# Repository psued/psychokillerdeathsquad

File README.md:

# Psycho Killer Death Squad - FPGA
Branch for Vivado project and docs/utilities for the FPGA.

## Vivado project setup
1. Inside of `fpga/scripts`, run the following command:
```
vivado -mode batch -source create_project.tcl -tclargs custom
```
2. In Vivado, open the .xpr file found inside `fpga/build/custom`

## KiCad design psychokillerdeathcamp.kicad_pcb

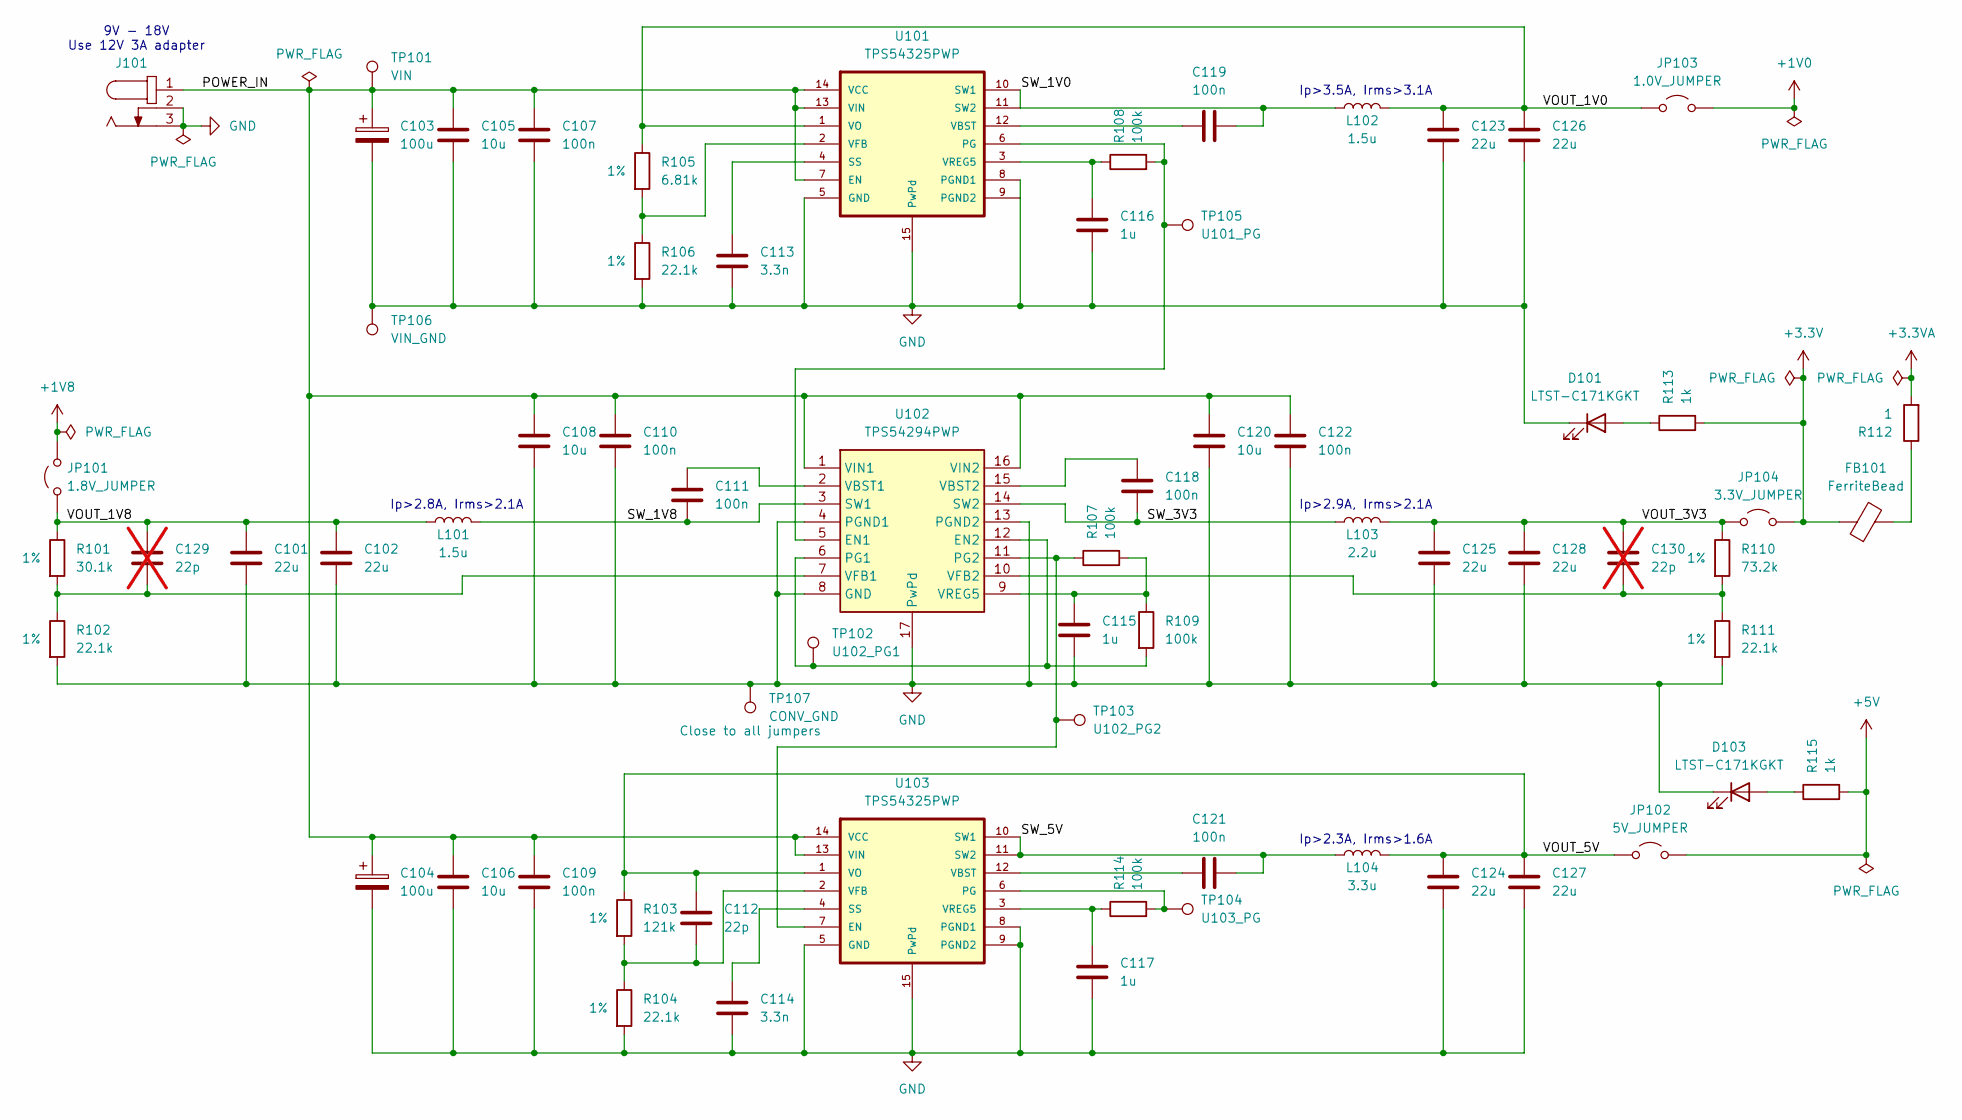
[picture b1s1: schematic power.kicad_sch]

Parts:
C101, C102, C123, C124, C125, C126, C127, C128: 22u; C_1206_3216Metric_Pad1.33x1.80mm_HandSolder
C103, C104: 100u; CP_Elec_6.3x7.7
C105, C106, C108, C120: 10u; C_1206_3216Metric_Pad1.33x1.80mm_HandSolder
C107, C109, C110, C111, C118, C119, C121, C122: 100n; C_0805_2012Metric_Pad1.18x1.45mm_HandSolder
C112: 22p; C_0805_2012Metric_Pad1.18x1.45mm_HandSolder
C113, C114: 3.3n; C_0805_2012Metric_Pad1.18x1.45mm_HandSolder
C115, C116, C117: 1u; C_0805_2012Metric_Pad1.18x1.45mm_HandSolder
C129, C130: 22p; C_0805_2012Metric_Pad1.18x1.45mm_HandSolder; not fitted
D101, D103: LTST-C171KGKT; LED_0805_2012Metric_Pad1.15x1.40mm_HandSolder
FB101: FerriteBead; L_0805_2012Metric_Pad1.05x1.20mm_HandSolder
J101: 694106301002; J_Wurth_WR-DC_694106301002; Working Voltage (V (DC)) 30; Part Number 694106301002
JP101: 1.8V_JUMPER; PinHeader_1x02_P2.54mm_Vertical
JP102: 5V_JUMPER; PinHeader_1x02_P2.54mm_Vertical
JP103: 1.0V_JUMPER; PinHeader_1x02_P2.54mm_Vertical
JP104: 3.3V_JUMPER; PinHeader_1x02_P2.54mm_Vertical
L101, L102: 1.5u; L_Taiyo-Yuden_NR-60xx_HandSoldering
L103: 2.2u; L_Taiyo-Yuden_NR-60xx_HandSoldering
L104: 3.3u; L_Taiyo-Yuden_NR-60xx_HandSoldering
R101: 30.1k; R_0805_2012Metric_Pad1.20x1.40mm_HandSolder; Tolerance 1%
R102, R104, R106, R111: 22.1k; R_0805_2012Metric_Pad1.20x1.40mm_HandSolder; Tolerance 1%
R103: 121k; R_0805_2012Metric_Pad1.20x1.40mm_HandSolder; Tolerance 1%
R105: 6.81k; R_0805_2012Metric_Pad1.20x1.40mm_HandSolder; Tolerance 1%
R107, R108, R109, R114: 100k; R_0805_2012Metric_Pad1.20x1.40mm_HandSolder
R110: 73.2k; R_0805_2012Metric_Pad1.20x1.40mm_HandSolder; Tolerance 1%
R112: 1; R_0805_2012Metric_Pad1.20x1.40mm_HandSolder
R113, R115: 1k; R_0805_2012Metric_Pad1.20x1.40mm_HandSolder
TP101: VIN; TestPoint_Pad_D1.5mm
TP102: U102_PG1; PinHeader_1x01_P2.54mm_Vertical
TP103: U102_PG2; PinHeader_1x01_P2.54mm_Vertical
TP104: U103_PG; PinHeader_1x01_P2.54mm_Vertical
TP105: U101_PG; PinHeader_1x01_P2.54mm_Vertical
TP106: VIN_GND; PinHeader_1x01_P2.54mm_Vertical
TP107: CONV_GND; PinHeader_1x01_P2.54mm_Vertical
U101, U103: TPS54325PWP; Texas_HTSSOP-14-1EP_4.4x5mm_P0.65mm_EP3.4x5mm_Mask2.60x2.59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
U102: TPS54294PWP; HTSSOP-16-1EP_4.4x5mm_P0.65mm_EP3.4x5mm_Mask3.30x3.30mm_The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; Mouser Part Number 595-TPS54294PWP

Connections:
+1V0: JP103.2 (B); also elsewhere on the board
+1V8: JP101.2 (B); also elsewhere on the board
+3.3V: FB101.1, JP104.2 (B), R113.2; also elsewhere on the board
+3.3VA: R112.2; also elsewhere on the board
+5V: JP102.2 (B), R115.2; also elsewhere on the board
/Power/POWER_IN: C103.1, C104.1, C105.1, C106.1, C107.1, C108.1, C109.1, C110.1, C120.1, C122.1, J101.1, TP101.1 (1_1), U101.7 (EN), U101.13 (VIN), U101.14 (VCC), U102.1 (VIN1), U102.16 (VIN2), U103.13 (VIN), U103.14 (VCC)
/Power/SW_1V0: C119.2, L102.1, U101.10 (SW1), U101.11 (SW2)
/Power/SW_1V8: C111.2, L101.2, U102.3 (SW1)
/Power/SW_3V3: C118.2, L103.1, U102.14 (SW2)
/Power/SW_5V: C121.2, L104.1, U103.10 (SW1), U103.11 (SW2)
/Power/VOUT_1V0: C123.1, C126.1, JP103.1 (A), L102.2, R105.1, U101.1 (VO)
/Power/VOUT_1V8: C101.1, C102.1, C129.1, JP101.1 (A), L101.1, R101.1
/Power/VOUT_3V3: C125.1, C128.1, C130.1, JP104.1 (A), L103.2, R110.1
/Power/VOUT_5V: C112.1, C124.1, C127.1, JP102.1 (A), L104.2, R103.1, U103.1 (VO)
GND: C101.2, C102.2, C103.2, C104.2, C105.2, C106.2, C107.2, C108.2, C109.2, C110.2, C113.2, C114.2, C115.2, C116.2, C117.2, C120.2, C122.2, C123.2, C124.2, C125.2, C126.2, C127.2, C128.2, D101.1 (K), D103.1 (K), J101.2, J101.3, R102.2, R104.2, R106.2, R111.2, TP106.1 (1_1), TP107.1 (1_1), U101.5 (GND), U101.8 (PGND1), U101.9 (PGND2), U101.15 (PwPd), U102.4 (PGND1), U102.8 (GND), U102.13 (PGND2), U102.17 (PwPd), U103.5 (GND), U103.8 (PGND1), U103.9 (PGND2), U103.15 (PwPd); also elsewhere on the board
unnamed: D101.2 (A), R113.1
unnamed: D103.2 (A), R115.1
unnamed: FB101.2, R112.1
unnamed: R108.2, TP105.1 (1_1), U101.6 (PG), U102.5 (EN1)
unnamed: C113.1, U101.4 (SS)
unnamed: C119.1, U101.12 (VBST)
unnamed: R105.2, R106.1, U101.2 (VFB)
unnamed: C116.1, R108.1, U101.3 (VREG5)
unnamed: R109.2, TP102.1 (1_1), U102.6 (PG1), U102.12 (EN2)
unnamed: R107.1, TP103.1 (1_1), U102.11 (PG2), U103.7 (EN)
unnamed: C111.1, U102.2 (VBST1)
unnamed: C118.1, U102.15 (VBST2)
unnamed: C129.2, R101.2, R102.1, U102.7 (VFB1)
unnamed: C130.2, R110.2, R111.1, U102.10 (VFB2)
unnamed: C115.1, R107.2, R109.1, U102.9 (VREG5)
unnamed: R114.2, TP104.1 (1_1), U103.6 (PG)
unnamed: C114.1, U103.4 (SS)
unnamed: C121.1, U103.12 (VBST)
unnamed: C112.2, R103.2, R104.1, U103.2 (VFB)
unnamed: C117.1, R114.1, U103.3 (VREG5)

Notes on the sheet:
Ip>2.9A, Irms>2.1A
Ip>2.8A, Irms>2.1A
9V - 18V Use 12V 3A adapter
Ip>3.5A, Irms>3.1A
Ip>2.3A, Irms>1.6A

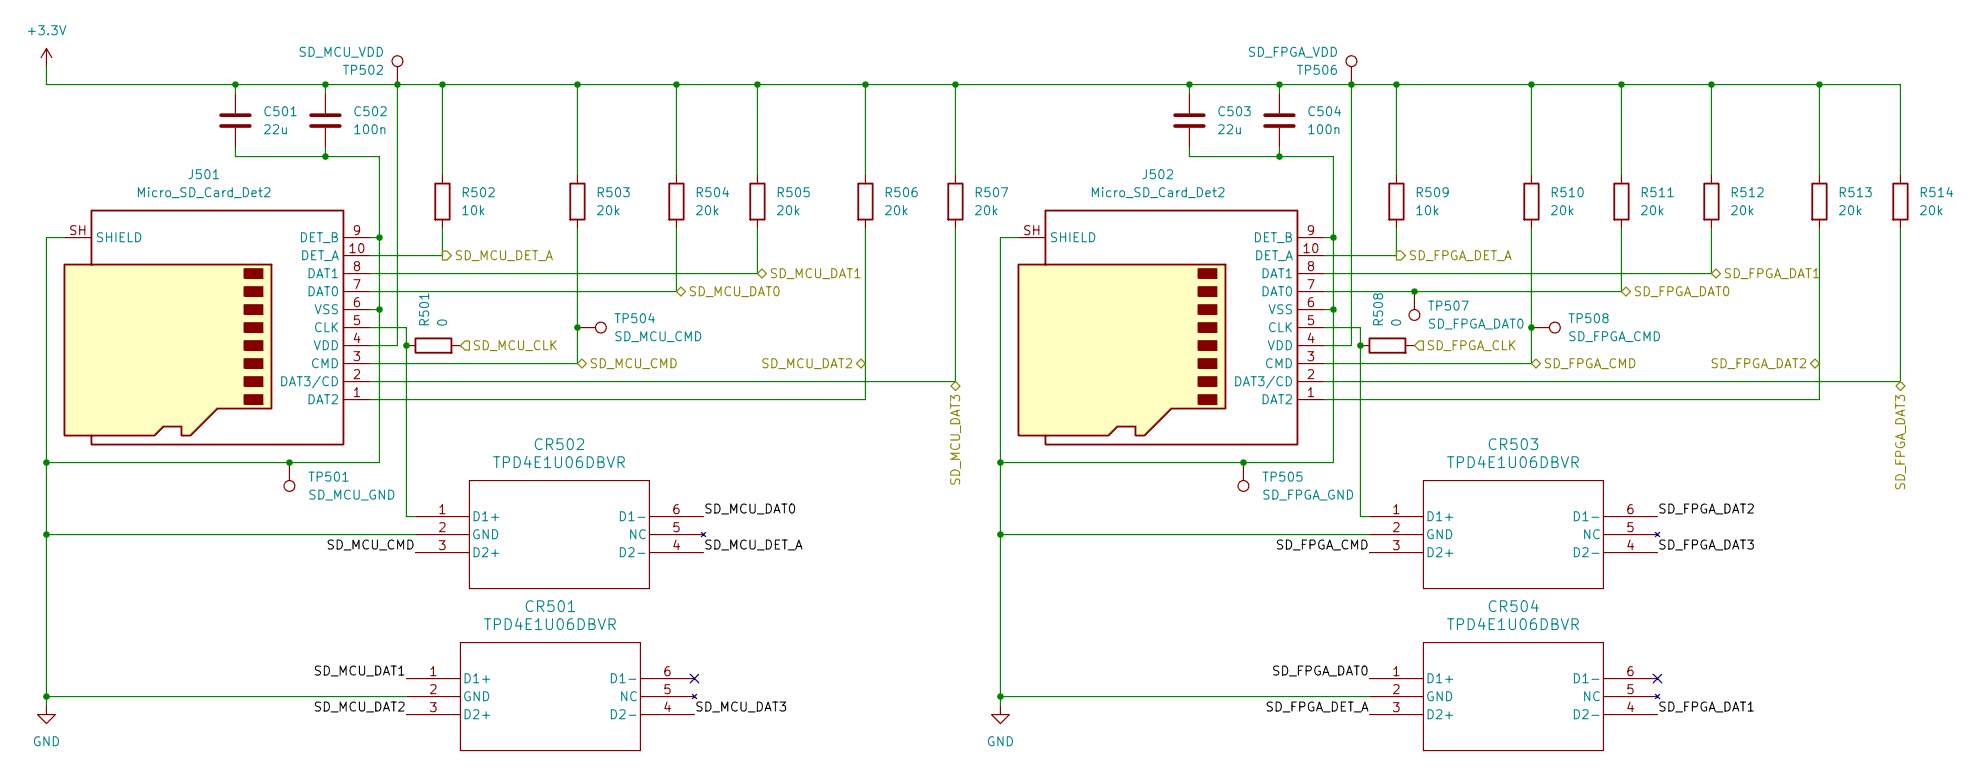
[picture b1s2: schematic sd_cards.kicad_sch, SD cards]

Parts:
C501, C503: 22u; C_1206_3216Metric_Pad1.33x1.80mm_HandSolder
C502, C504: 100n; C_0805_2012Metric_Pad1.18x1.45mm_HandSolder
CR501, CR502, CR503, CR504: TPD4E1U06DBVR
J501, J502: Micro_SD_Card_Det2; 5033981892
R501, R508: 0; R_0805_2012Metric_Pad1.20x1.40mm_HandSolder
R502, R509: 10k; R_0805_2012Metric_Pad1.20x1.40mm_HandSolder
R503, R504, R505, R506, R507, R510, R511, R512, R513, R514: 20k; R_0805_2012Metric_Pad1.20x1.40mm_HandSolder
TP501: SD_MCU_GND; PinHeader_1x01_P2.54mm_Vertical
TP502: SD_MCU_VDD; TestPoint_Pad_D1.5mm
TP504: SD_MCU_CMD; PinHeader_1x01_P2.54mm_Vertical
TP505: SD_FPGA_GND; PinHeader_1x01_P2.54mm_Vertical
TP506: SD_FPGA_VDD; TestPoint_Pad_D1.5mm
TP507: SD_FPGA_DAT0; PinHeader_1x01_P2.54mm_Vertical
TP508: SD_FPGA_CMD; PinHeader_1x01_P2.54mm_Vertical

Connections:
+3.3V: C501.1, C502.1, C503.1, C504.1, J501.4 (VDD), J502.4 (VDD), R502.1, R503.1, R504.1, R505.1, R506.1, R507.1, R509.1, R510.1, R511.1, R512.1, R513.1, R514.1, TP502.1 (1_1), TP506.1 (1_1); also elsewhere on the board
/MCU/SD_MCU_CLK: R501.2; also elsewhere on the board
/SD cards/SD_FPGA_CLK: R508.2; also elsewhere on the board
/SD cards/SD_FPGA_CMD: CR503.3 (D2+), J502.3 (CMD), R510.2, TP508.1 (1_1); also elsewhere on the board
/SD cards/SD_FPGA_DAT0: CR504.1 (D1+), J502.7 (DAT0), R511.2, TP507.1 (1_1); also elsewhere on the board
/SD cards/SD_FPGA_DAT1: CR504.4 (D2-), J502.8 (DAT1), R512.2; also elsewhere on the board
/SD cards/SD_FPGA_DAT2: CR503.6 (D1-), J502.1 (DAT2), R513.2; also elsewhere on the board
/SD cards/SD_FPGA_DAT3: CR503.4 (D2-), J502.2 (DAT3/CD), R514.2; also elsewhere on the board
/SD cards/SD_FPGA_DET_A: CR504.3 (D2+), J502.10 (DET_A), R509.2; also elsewhere on the board
/SD cards/SD_MCU_CMD: CR502.3 (D2+), J501.3 (CMD), R503.2, TP504.1 (1_1); also elsewhere on the board
/SD cards/SD_MCU_DAT0: CR502.6 (D1-), J501.7 (DAT0), R504.2; also elsewhere on the board
/SD cards/SD_MCU_DAT1: CR501.1 (D1+), J501.8 (DAT1), R505.2; also elsewhere on the board
/SD cards/SD_MCU_DAT2: CR501.3 (D2+), J501.1 (DAT2), R506.2; also elsewhere on the board
/SD cards/SD_MCU_DAT3: CR501.4 (D2-), J501.2 (DAT3/CD), R507.2; also elsewhere on the board
/SD cards/SD_MCU_DET_A: CR502.4 (D2-), J501.10 (DET_A), R502.2; also elsewhere on the board
GND: C501.2, C502.2, C503.2, C504.2, CR501.2 (GND), CR502.2 (GND), CR503.2 (GND), CR504.2 (GND), J501.6 (VSS), J501.9 (DET_B), J501.SH (SHIELD), J502.6 (VSS), J502.9 (DET_B), J502.SH (SHIELD), TP501.1 (1_1), TP505.1 (1_1); also elsewhere on the board
unnamed: CR502.1 (D1+), J501.5 (CLK), R501.1
unnamed: CR503.1 (D1+), J502.5 (CLK), R508.1

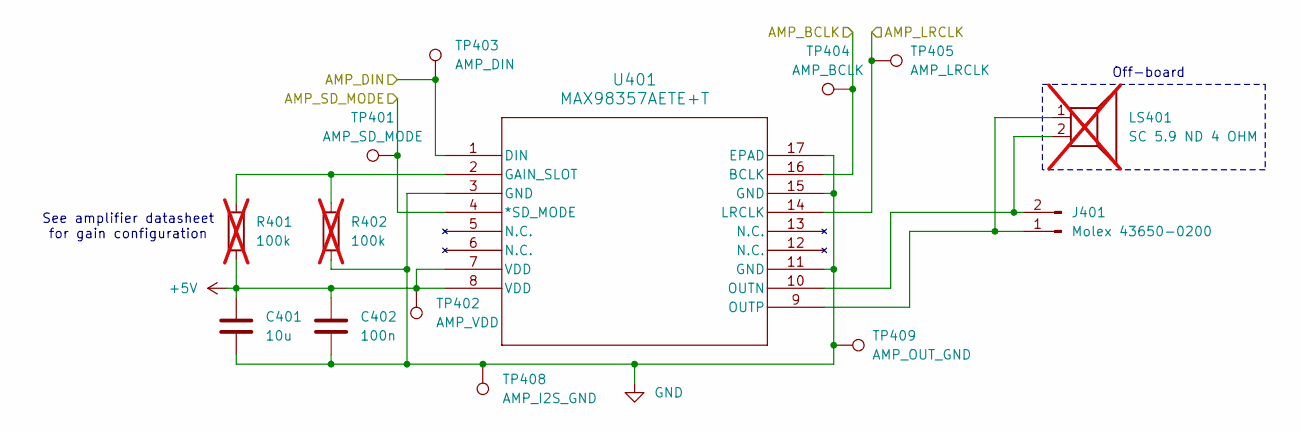
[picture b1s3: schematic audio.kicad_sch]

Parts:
C401: 10u; C_0805_2012Metric_Pad1.18x1.45mm_HandSolder
C402: 100n; C_0805_2012Metric_Pad1.18x1.45mm_HandSolder
J401: Molex 43650-0200; Molex_Micro-Fit_3.0_43650-0200_1x02_P3.00mm_Horizontal
LS401: SC 5.9 ND 4 OHM; not fitted
R401, R402: 100k; R_0805_2012Metric_Pad1.20x1.40mm_HandSolder; not fitted
TP401: AMP_SD_MODE; TestPoint_Pad_D1.5mm
TP402: AMP_VDD; TestPoint_Pad_D1.5mm
TP403: AMP_DIN; PinHeader_1x01_P2.54mm_Vertical
TP404: AMP_BCLK; PinHeader_1x01_P2.54mm_Vertical
TP405: AMP_LRCLK; PinHeader_1x01_P2.54mm_Vertical
TP408: AMP_I2S_GND; PinHeader_1x01_P2.54mm_Vertical
TP409: AMP_OUT_GND; PinHeader_1x01_P2.54mm_Vertical
U401: MAX98357AETE+T; 21-0136I_T1633-4_MXM-M

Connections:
+5V: C401.1, C402.1, R401.2, TP402.1 (1_1), U401.7 (VDD), U401.8 (VDD); also elsewhere on the board
/Audio/AMP_BCLK: TP404.1 (1_1), U401.16 (BCLK); also elsewhere on the board
/Audio/AMP_DIN: TP403.1 (1_1), U401.1 (DIN); also elsewhere on the board
/Audio/AMP_LRCLK: TP405.1 (1_1), U401.14 (LRCLK); also elsewhere on the board
/Audio/AMP_SD_MODE: TP401.1 (1_1), U401.4 (*SD_MODE); also elsewhere on the board
GND: C401.2, C402.2, R402.2, TP408.1 (1_1), TP409.1 (1_1), U401.3 (GND), U401.11 (GND), U401.15 (GND), U401.17 (EPAD); also elsewhere on the board
unnamed: J401.1, LS401.1, U401.9 (OUTP)
unnamed: J401.2, LS401.2, U401.10 (OUTN)
unnamed: R401.1, R402.1, U401.2 (GAIN_SLOT)

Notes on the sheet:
Off-board
See amplifier datasheet for gain configuration

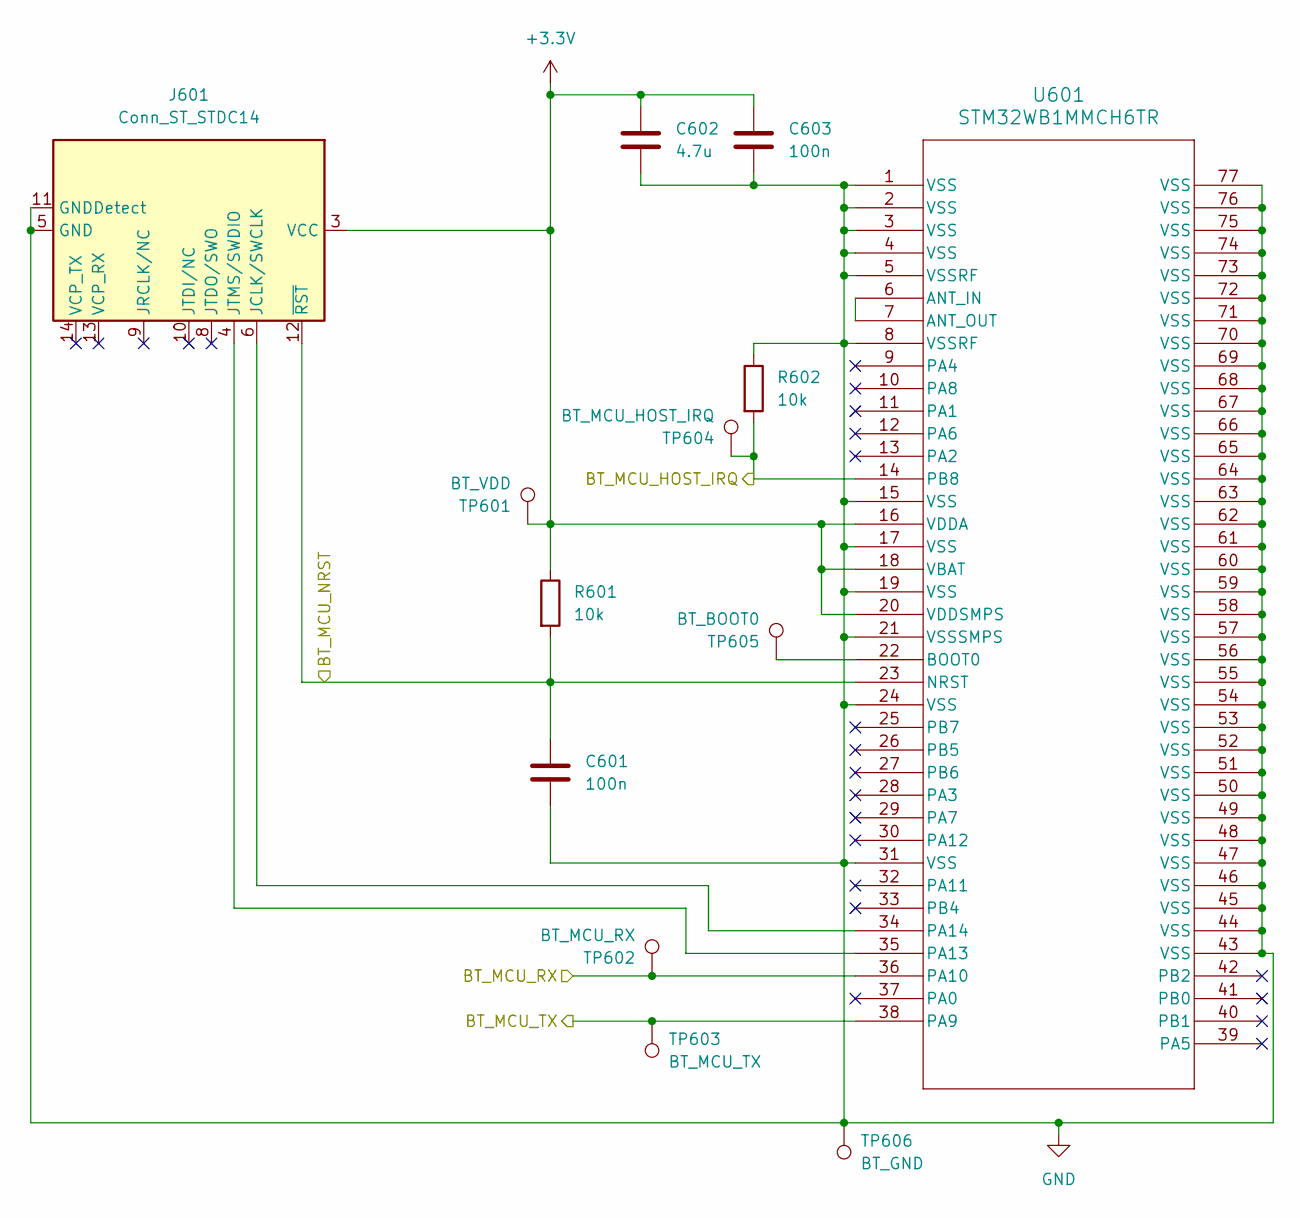
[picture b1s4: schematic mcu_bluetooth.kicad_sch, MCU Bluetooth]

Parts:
C601, C603: 100n; C_0805_2012Metric_Pad1.18x1.45mm_HandSolder
C602: 4.7u; C_0805_2012Metric_Pad1.18x1.45mm_HandSolder
J601: Conn_ST_STDC14; CONN_FTSH-x07-01-x-DV-K-A_SAI
R601, R602: 10k; R_0805_2012Metric_Pad1.20x1.40mm_HandSolder
TP601: BT_VDD; TestPoint_Pad_D1.5mm
TP602: BT_MCU_RX; PinHeader_1x01_P2.54mm_Vertical
TP603: BT_MCU_TX; PinHeader_1x01_P2.54mm_Vertical
TP604: BT_MCU_HOST_IRQ; PinHeader_1x01_P2.54mm_Vertical
TP605: BT_BOOT0; TestPoint_Pad_D1.5mm
TP606: BT_GND; PinHeader_1x01_P2.54mm_Vertical
U601: STM32WB1MMCH6TR; LGA77_6P5X10_STM

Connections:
+3.3V: C602.1, C603.1, J601.3 (VCC), R601.1, TP601.1 (1_1), U601.16 (VDDA), U601.18 (VBAT), U601.20 (VDDSMPS); also elsewhere on the board
/MCU Bluetooth/BT_MCU_HOST_IRQ: R602.2, TP604.1 (1_1), U601.14 (PB8); also elsewhere on the board
/MCU Bluetooth/BT_MCU_NRST: C601.1, J601.12 (~RST), R601.2, U601.23 (NRST); also elsewhere on the board
/MCU Bluetooth/BT_MCU_RX: TP602.1 (1_1), U601.36 (PA10); also elsewhere on the board
/MCU Bluetooth/BT_MCU_TX: TP603.1 (1_1), U601.38 (PA9); also elsewhere on the board
GND: C601.2, C602.2, C603.2, J601.5 (GND), J601.7 (GND), J601.11 (GNDDetect), R602.1, TP606.1 (1_1), U601.1 (VSS), U601.2 (VSS), U601.3 (VSS), U601.4 (VSS), U601.5 (VSSRF), U601.8 (VSSRF), U601.15 (VSS), U601.17 (VSS), U601.19 (VSS), U601.21 (VSSSMPS), U601.24 (VSS), U601.31 (VSS), U601.43 (VSS), U601.44 (VSS), U601.45 (VSS), U601.46 (VSS), U601.47 (VSS), U601.48 (VSS), U601.49 (VSS), U601.50 (VSS), U601.51 (VSS), U601.52 (VSS), U601.53 (VSS), U601.54 (VSS), U601.55 (VSS), U601.56 (VSS), U601.57 (VSS), U601.58 (VSS), U601.59 (VSS), U601.60 (VSS), U601.61 (VSS), U601.62 (VSS), U601.63 (VSS), U601.64 (VSS), U601.65 (VSS), U601.66 (VSS), U601.67 (VSS), U601.68 (VSS), U601.69 (VSS), U601.70 (VSS), U601.71 (VSS), U601.72 (VSS), U601.73 (VSS), U601.74 (VSS), U601.75 (VSS), U601.76 (VSS), U601.77 (VSS); also elsewhere on the board
unnamed: J601.6 (JCLK/SWCLK), U601.34 (PA14)
unnamed: J601.4 (JTMS/SWDIO), U601.35 (PA13)
unnamed: U601.6 (ANT_IN), U601.7 (ANT_OUT)
unnamed: TP605.1 (1_1), U601.22 (BOOT0)

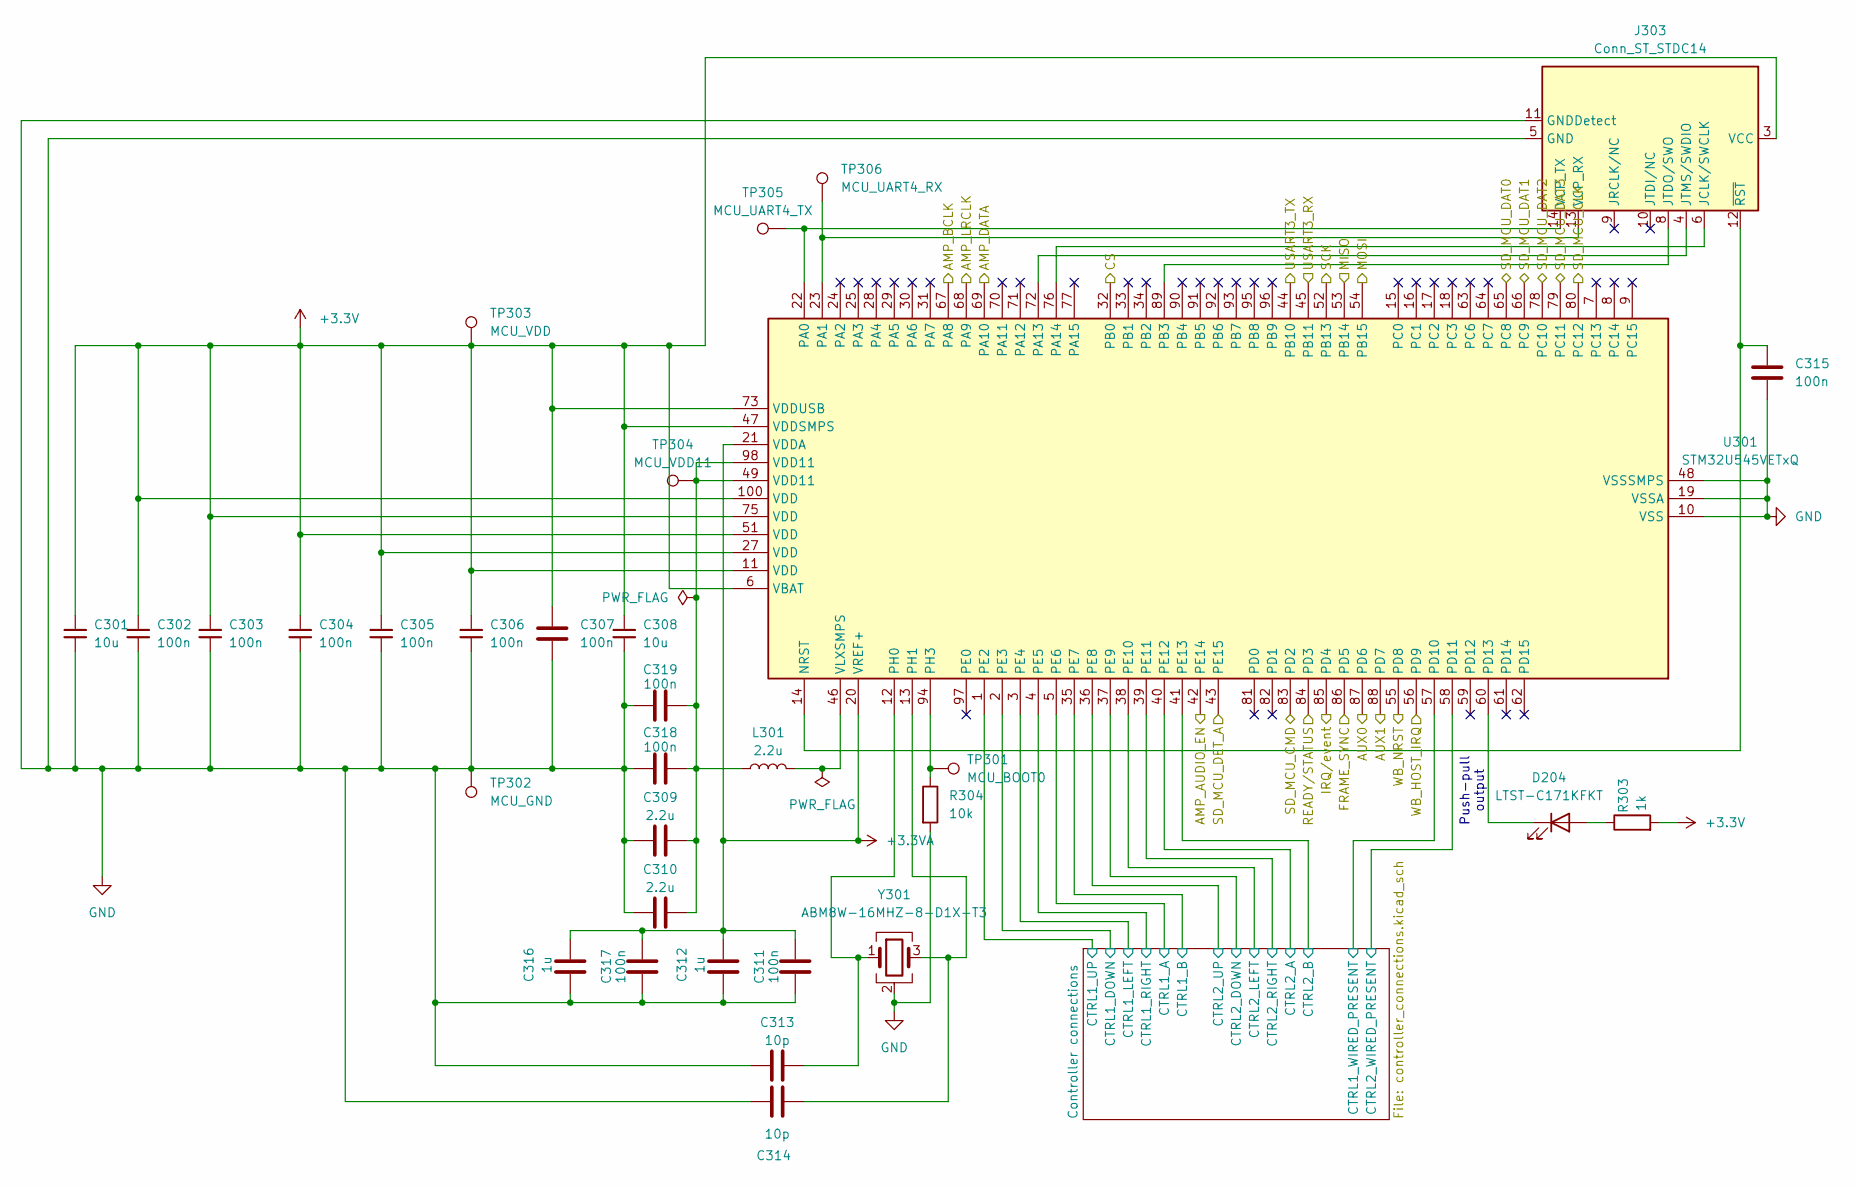
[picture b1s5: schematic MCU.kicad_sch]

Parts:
C301, C308: 10u; C_0805_2012Metric_Pad1.18x1.45mm_HandSolder
C302, C303, C304, C305, C306, C307, C311, C315, C317, C318, C319: 100n; C_0805_2012Metric_Pad1.18x1.45mm_HandSolder
C309, C310: 2.2u; C_0805_2012Metric_Pad1.18x1.45mm_HandSolder
C312, C316: 1u; C_0805_2012Metric_Pad1.18x1.45mm_HandSolder
C313, C314: 10p; C_0805_2012Metric_Pad1.18x1.45mm_HandSolder
D204: LTST-C171KFKT; LED_0805_2012Metric_Pad1.15x1.40mm_HandSolder
J303: Conn_ST_STDC14; CONN_FTSH-x07-01-x-DV-K-A_SAI
L301: 2.2u; IND_IHHP-0805ZH-01_VIS-M
R303: 1k; R_0805_2012Metric_Pad1.20x1.40mm_HandSolder
R304: 10k; R_0805_2012Metric_Pad1.20x1.40mm_HandSolder
TP301: MCU_BOOT0; TestPoint_Pad_D1.5mm
TP302: MCU_GND; PinHeader_1x01_P2.54mm_Vertical
TP303: MCU_VDD; TestPoint_Pad_D1.5mm
TP304: MCU_VDD11; TestPoint_Pad_D1.5mm
TP305: MCU_UART4_TX; TestPoint_Pad_D1.5mm
TP306: MCU_UART4_RX; TestPoint_Pad_D1.5mm
U301: STM32U545VETxQ; LQFP-100_14x14mm_P0.5mm
Y301: ABM8W-16MHZ-8-D1X-T3; Crystal_SMD_Abracon_ABM8AIG-4Pin_3.2x2.5mm

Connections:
+3.3V: C301.1, C302.1, C303.1, C304.1, C305.1, C306.1, C307.1, C308.1, J303.3 (VCC), R303.2, TP303.1 (1_1), U301.6 (VBAT), U301.11 (VDD), U301.27 (VDD), U301.47 (VDDSMPS), U301.51 (VDD), U301.73 (VDDUSB), U301.75 (VDD), U301.100 (VDD); also elsewhere on the board
+3.3VA: C311.2, C312.1, C316.1, C317.2, U301.20 (VREF+), U301.21 (VDDA); also elsewhere on the board
/Audio/AMP_BCLK: U301.67 (PA8); also elsewhere on the board
/Audio/AMP_DIN: U301.69 (PA10); also elsewhere on the board
/Audio/AMP_LRCLK: U301.68 (PA9); also elsewhere on the board
/Audio/AMP_SD_MODE: U301.42 (PE14); also elsewhere on the board
/MCU Bluetooth/BT_MCU_HOST_IRQ: U301.56 (PD9); also elsewhere on the board
/MCU Bluetooth/BT_MCU_NRST: U301.55 (PD8); also elsewhere on the board
/MCU Bluetooth/BT_MCU_RX: U301.44 (PB10); also elsewhere on the board
/MCU Bluetooth/BT_MCU_TX: U301.45 (PB11); also elsewhere on the board
/MCU/AUX0: U301.87 (PD6); also elsewhere on the board
/MCU/AUX1: U301.88 (PD7); also elsewhere on the board
/MCU/CS: U301.32 (PB0); also elsewhere on the board
/MCU/Controller connections/CTRL1_A: U301.5 (PE6); also elsewhere on the board
/MCU/Controller connections/CTRL1_B: U301.35 (PE7); also elsewhere on the board
/MCU/Controller connections/CTRL1_DOWN: U301.2 (PE3); also elsewhere on the board
/MCU/Controller connections/CTRL1_LEFT: U301.3 (PE4); also elsewhere on the board
/MCU/Controller connections/CTRL1_RIGHT: U301.4 (PE5); also elsewhere on the board
/MCU/Controller connections/CTRL1_UP: U301.1 (PE2); also elsewhere on the board
/MCU/Controller connections/CTRL1_WIRED_PRESENT: U301.57 (PD10); also elsewhere on the board
/MCU/Controller connections/CTRL2_A: U301.40 (PE12); also elsewhere on the board
/MCU/Controller connections/CTRL2_B: U301.41 (PE13); also elsewhere on the board
/MCU/Controller connections/CTRL2_DOWN: U301.37 (PE9); also elsewhere on the board
/MCU/Controller connections/CTRL2_LEFT: U301.38 (PE10); also elsewhere on the board
/MCU/Controller connections/CTRL2_RIGHT: U301.39 (PE11); also elsewhere on the board
/MCU/Controller connections/CTRL2_UP: U301.36 (PE8); also elsewhere on the board
/MCU/Controller connections/CTRL2_WIRED_PRESENT: U301.58 (PD11); also elsewhere on the board
/MCU/MISO: U301.53 (PB14); also elsewhere on the board
/MCU/MOSI: U301.54 (PB15); also elsewhere on the board
/MCU/SCK: U301.52 (PB13); also elsewhere on the board
/MCU/SD_MCU_CLK: U301.80 (PC12); also elsewhere on the board
/SD cards/SD_MCU_CMD: U301.83 (PD2); also elsewhere on the board
/SD cards/SD_MCU_DAT0: U301.65 (PC8); also elsewhere on the board
/SD cards/SD_MCU_DAT1: U301.66 (PC9); also elsewhere on the board
/SD cards/SD_MCU_DAT2: U301.78 (PC10); also elsewhere on the board
/SD cards/SD_MCU_DAT3: U301.79 (PC11); also elsewhere on the board
/SD cards/SD_MCU_DET_A: U301.43 (PE15); also elsewhere on the board
/fpga/FRAME_SYNC: U301.86 (PD5); also elsewhere on the board
/fpga/IRQ/event: U301.85 (PD4); also elsewhere on the board
/fpga/READY/STATUS: U301.84 (PD3); also elsewhere on the board
GND: C301.2, C302.2, C303.2, C304.2, C305.2, C306.2, C307.2, C308.2, C309.1, C310.1, C311.1, C312.2, C313.1, C314.1, C315.2, C316.2, C317.1, C318.1, C319.1, J303.5 (GND), J303.7 (GND), J303.11 (GNDDetect), R304.2, TP302.1 (1_1), U301.10 (VSS), U301.19 (VSSA), U301.26 (VSS), U301.48 (VSSSMPS), U301.50 (VSS), U301.74 (VSS), U301.99 (VSS), Y301.2 (G), Y301.4 (G); also elsewhere on the board
unnamed: C309.2, C310.2, C318.2, C319.2, L301.1, TP304.1 (1_1), U301.49 (VDD11), U301.98 (VDD11)
unnamed: D204.2 (A), R303.1
unnamed: D204.1 (K), U301.60 (PD13)
unnamed: J303.6 (JCLK/SWCLK), U301.76 (PA14)
unnamed: J303.8 (JTDO/SWO), U301.89 (PB3)
unnamed: J303.4 (JTMS/SWDIO), U301.72 (PA13)
unnamed: J303.13 (VCP_RX), TP306.1 (1_1), U301.23 (PA1)
unnamed: J303.14 (VCP_TX), TP305.1 (1_1), U301.22 (PA0)
unnamed: C315.1, J303.12 (~RST), U301.14 (NRST)
unnamed: C313.2, U301.12 (PH0), Y301.1
unnamed: C314.2, U301.13 (PH1), Y301.3
unnamed: R304.1, TP301.1 (1_1), U301.94 (PH3)
unnamed: L301.2, U301.46 (VLXSMPS)

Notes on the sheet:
Push-pull output
